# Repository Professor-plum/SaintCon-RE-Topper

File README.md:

# SaintCon 2024 Badge RE Topper
A reverse engineering themed SaintCon 2024 badge topper

This topper can blink the LEDs in one of four patterns that can be selected by touching the skull (captive touch)

## Bill of Materials 
* 1x PY32F002AA15M
* 2x OSRAM TOPLED LS T77K LEDs
* 1x 470 Ohm 0805 Resistor
* 1x 1M Ohm 0805 Resistor
* 1x 1uF 0805 Capacitor

## Assembly instructions
1. Solder on the py32 microcontroller paying attention to pin 1 orientation
2. Solder on the 2 LEDs paying attention to direction. 
	- The black mark should be towards the bottom of the badge.
3. Solder on the 2 resistors, orientation doesn't matter
	- R1 is the 470 ohm resistor (4700 marking) 
	- R2 is the 1M ohm resistor (105 marking)
4. Solder on the capacitor, orientation doesn't matter

## Flashing instructions
> [!NOTE]
>If you obtained the components during Saintcon the py32 is already flashed and you can skip the remainder of these steps.

Required hardware & software
- ST-Link V2 clone
- PyOCD [https://pyocd.io/](https://pyocd.io/) installed.

Connect 3.3V, GND, SWDIO, SWCLK, and RST to the ST-Link. These are all broken out on the 2x3 1.00mm pin header.

To flash the MCU just execute `make flash` from the Fimware directory.

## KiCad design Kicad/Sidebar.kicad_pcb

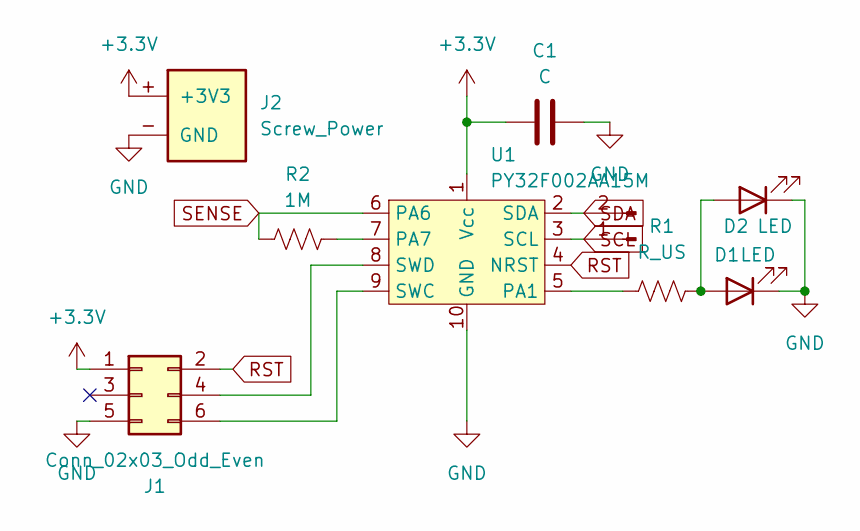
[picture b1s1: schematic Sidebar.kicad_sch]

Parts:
C1: C; C_0805_2012Metric_Pad1.18x1.45mm_HandSolder
D1, D2: LED; Reverse_LED
J1: Conn_02x03_Odd_Even; PinHeader_2x03_P1.27mm_Vertical
J2: Screw_Power; Saintcon2024Klip-onUpper
J3: Conn_01x02_Pin; PinHeader_1x02_P2.54mm_Vertical
R1: R_US; R_0805_2012Metric_Pad1.20x1.40mm_HandSolder
R2: 1M; R_0805_2012Metric_Pad1.20x1.40mm_HandSolder
U1: PY32F002AA15M; SSOP-10_3.9x4.9mm_P1.00mm

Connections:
+3.3V: C1.1, J1.1, J2.+ (+3V3), U1.1 (Vcc)
GND: C1.2, D1.1 (K), D2.1 (K), J1.5, J2.- (GND), U1.10 (GND)
unnamed: D1.2 (A), D2.2 (A), R1.1
unnamed: J1.4, U1.8 (SWD)
unnamed: J1.6, U1.9 (SWC)
unnamed: R1.2, U1.5 (PA1)
unnamed: R2.1, U1.7 (PA7)
RST: J1.2, U1.4 (NRST)
SCL: J3.1, U1.3 (SCL)
SDA: J3.2, U1.2 (SDA)
SENSE: R2.2, U1.6 (PA6)

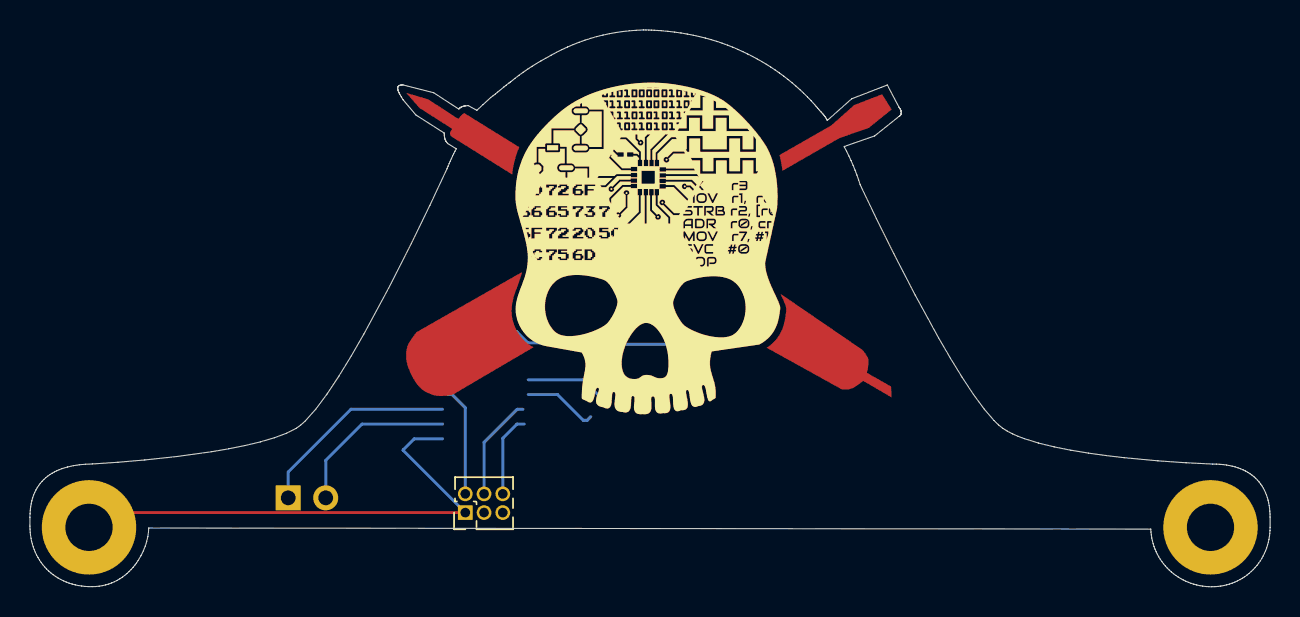
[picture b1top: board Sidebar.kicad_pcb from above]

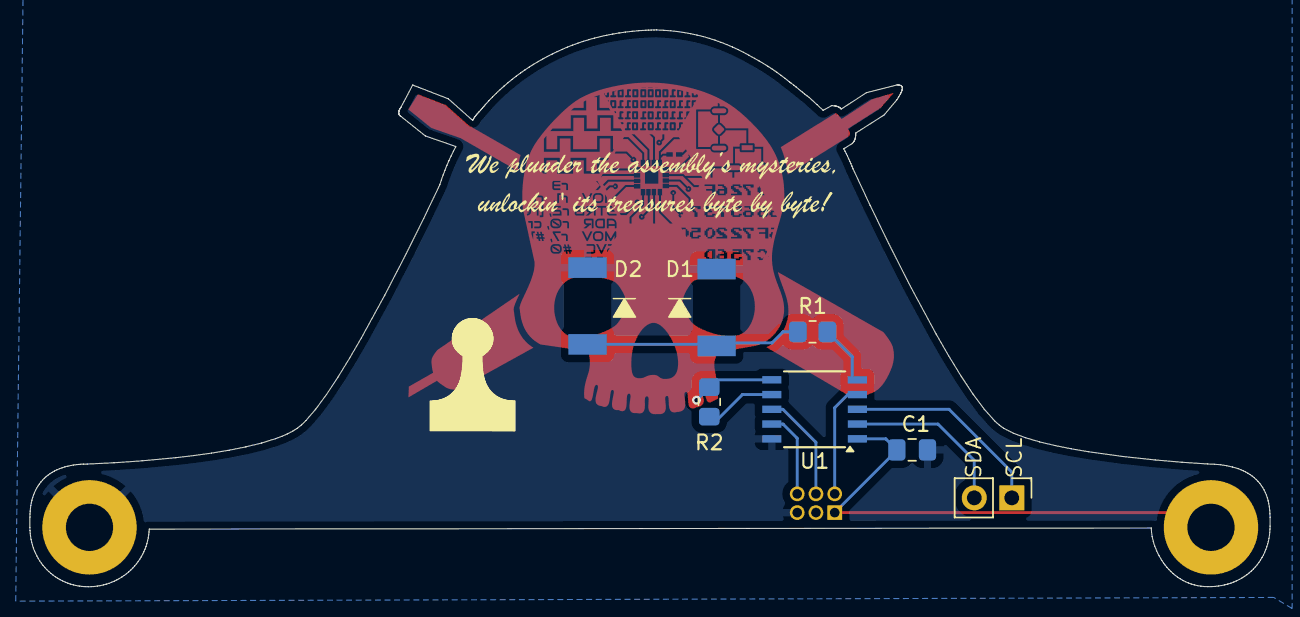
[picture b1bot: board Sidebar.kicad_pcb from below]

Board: 2 copper layers, 84.0 x 37.7 mm, 9 parts (7 on the bottom side), 11 nets.

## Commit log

2024-09-13 Updated Firmware
2024-09-13 Updated Kicad Files
2024-09-13 First pass at the Readme
2024-09-13 Fixing typos
2024-09-30 Updated firmware and readme with LED patterns
2024-10-23 Update README.md
    Corrected resistor values to match what was delivered
2024-10-25 Improvments made during Saintcon
